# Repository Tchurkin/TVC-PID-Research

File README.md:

# Quantifying Stability Boundaries for Amateur TVC Rockets (STS 2027)

This repository builds and validates a free, open-source **stability-mapping and preflight workflow** for small thrust-vector-control rockets. The goal is to replace hobbyist "tune until it flies" practice with a quantitative answer to a harder question: is a candidate rocket easy, fragile, or fundamentally infeasible given its real actuator and airframe?

## Mission
Give amateur and student TVC builders a quantitative preflight answer before they fly: is this rocket stabilizable at all, what hardware parameters matter most, and what starting gains are justified by the measured actuator rather than copied from another project.

## Core Contribution
This project does **not** claim new control theory. It contributes a *measurement-to-decision pipeline* and a quantitative stability map that do not currently exist in the amateur TVC community:
1. Bench measurement of loaded actuator slew, travel, deadband, and backlash.
2. Realistic flight model with documented sensor and actuator nonidealities.
3. Empirically calibrated easy / fragile / infeasible regime map plus GO / MARGINAL / NOGO classifier.
4. Bench-calibrated PD autotuner that beats copied or over-clean-sim gains in the workable region.
5. Regime-specific sim-to-real ablation that tells builders which parts of the reality gap actually matter where.
6. An explicitly secondary severe-collapse controller appendix, kept only where it survives honest stress tests.

## Headline Results (simulation-side, May 2026)
- **Scaling law:** required loaded slew rate ≈ `0.32 · p^2` (R² = 0.75), matching inverted-pendulum theory.
- **Firmware audit:** three publicly deployed open-source TVC firmwares all fail predictably on statically unstable airframes with their shipped PID gains.
- **Validator calibration** on held-out random configs: GO precision 91%, NOGO precision 100%.
- **Measured-aware tuning:** measured-plant PD beats naive-sim or copied-gain baselines in several hard cells.
- **Regime-aware realism screen:** actuator nonlinearity dominates the actuator-limited regime; sensor noise and effectiveness drift dominate near the boundary.
- **Hobby-range controller check:** in `experiments/results/pid_slew_regime_summary.csv`, a best-tuned sweep over nominal loaded slew 45-90 deg/s, `p = 4, 6, 8`, and retained slew scales 1.00-0.25 yields `48/48 BOTH_FINE` for PID and PID_SLEW_AWARE.
- **Severe-collapse appendix:** in the explicit legacy stress probe `experiments/results/pid_slew_probe.csv`, the lightweight slew-aware PID branch can still rescue some low-slew collapse cells, but that is no longer the main claim.

Current nominal sim stack: 75 deg/s loaded gimbal slew. The old ~15 deg/s stack is retained only in explicit severe-collapse controller stress scripts.

## Workspace Map
- `experiments/` — main evidence-generation scripts (validator, scaling law, ablations, comparisons) and `experiments/validator/recommend_envelope.m`.
- `experiments/run_pid_slew_regime_map.m` — honest hobby-range check for whether the lightweight controller matters once the nominal actuator is realistic.
- `experiments/results/` — CSVs and PNGs for every claim; `experiments/results/graphs/preflight_workflow.png` is the headline figure.
- `tools/bench_to_validator.m`, `tools/bench_to_autotune.m`, `tools/process_gimbal_bench_test.m` — bench-CSV → validator pipeline.
- `Firmware/feedback_servo_calibration.ino` — bench-rig firmware (analog-feedback servo data).
- `ModelRocket_Adaptive_TVC/src/simulate_case_realistic.m` — realistic flight simulator.
- `paper/Tentative_Paper_Draft.md`, `paper/Mentor_Project_Summary.md` — current paper framing.
- `data/bench/` — bench-test templates and (eventually) real measurements.

Older directories (`Direction_B_RC_ADRC_PathFollow/`, `supporting/Direction_C_Companion/`) are exploratory branches from earlier directions; they are retained for reference but are not on the current primary path.

## Quick Start
### Regenerate the headline figures
```powershell
cd experiments
& "C:/Program Files/MATLAB/R2026a/bin/matlab.exe" -batch "generate_preflight_workflow_figure; generate_phase_diagram_reference_vehicles; run_current_vs_proposed_practice; generate_preflight_story_figures;"
```

### Run the bench-to-autotune bridge on a bench CSV
```matlab
addpath(genpath('tools'));
addpath(genpath('ModelRocket_Adaptive_TVC/src'));
addpath('experiments/validator');
result = bench_to_autotune('data/bench/gimbal_bench_test_template.csv');
disp(result);
```

### Rebuild all simulator-side sweeps (slow)
```powershell
cd experiments
& "C:/Program Files/MATLAB/R2026a/bin/matlab.exe" -batch "run('run_s2r_ablation.m'); run('run_p_estimation_error.m'); run('run_basic_vs_better_sim.m');"
```

## Direction Anchor Files
- `paper/Tentative_Paper_Draft.md` — the paper draft (builder-voice abstract + intro).
- `paper/Mentor_Project_Summary.md` — short mentor-facing summary.
- `experiments/HEADLINE_FINAL.md` — locked simulator-side findings.
- `experiments/results/graphs/preflight_workflow.png` — one-page workflow diagram.
- `experiments/results/graphs/phase_diagram_reference_vehicles.png` — phase diagram with hobbyist reference dots.

## STS Framing
This is positioned as a *quantitative stability-boundary and preflight workflow paper for an underserved community*, not as a new-controller paper. The right STS comparison set is past finalists who built useful, reproducible, community-facing engineering artifacts and validated them with real measurements — not past finalists who claimed new physics or new control theory. The lightweight controller branch is now explicitly appendix-level unless future hardware data proves otherwise.

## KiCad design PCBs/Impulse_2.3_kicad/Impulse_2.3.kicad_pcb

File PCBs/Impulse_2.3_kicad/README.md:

# Impulse 2.3 — upsized pyro switching path

Forked from the **ordered** Impulse 2.2 files (the state manufactured 2026-08-01) on 2026-08-12,
after **Q21, the pyro rail ARM switch, burned out on the bench**. Revised 2026-08-13 once the
initiator was actually measured.

## The design point moved

The initiator measures **~0.3 Ω**, not the ~1 Ω the firmware comments assumed. That puts the firing
loop at **12–17 A**, against the 2–4 A the 2026-07-23 log entry sized the board for. At 14 A held for
the firmware's 900 ms:

| part | P | ΔT over 900 ms | verdict |
|---|---|---|---|
| AO3401A SOT-23 (the part that died) | 16.5 W | ~2100 °C | obliterated — fully explains the failure |
| CSD17313Q2 SON 2×2 (original firing FETs) | 11.5 W | ~254 °C | **would also fail** on a sustained pulse |

So the whole switching path is upsized, not just the part that died.

## What changed

Nothing outside these **six** parts: a netlist diff against 2.2 shows **77 nets in both, none added
or removed, and zero membership changes outside the swapped FETs**.

| | 2.2 | 2.3 |
|---|---|---|
| Q20 main battery switch (P-ch) | AO3401A, SOT-23 | **AON6403**, DFN 5×6 — LCSC **C2760089** |
| Q21 arm switch (P-ch) | AO3401A, SOT-23 | **AON6403**, DFN 5×6 — LCSC **C2760089** |
| Q21 R<sub>DS(on)</sub> | 60 mΩ @ −4.5 V | **4.3 mΩ @ −4.5 V** |
| Q16–Q19 firing FETs (N-ch) | CSD17313Q2, SON 2×2 | **CSD17301Q5A**, SON 5×6 — LCSC **C129940** |
| Q16–Q19 R<sub>DS(on)</sub> | 42 mΩ @ 3 V | **2.9 mΩ @ 3 V** |
| loop on-resistance | 84 mΩ hot | **10 mΩ hot** |
| drain → connector | trace | trace (see correction below) |
| pyro rail copper | 1.0 mm | 1.2–2.5 mm |

At 20 A / 900 ms the two halves are **matched**: **2.4 W** in each AON6403 (Tj ≈ 44 °C; survives the
pulse *indefinitely* — Tj ≈ 121 °C even at steady state) and **2.1 W** in each CSD17301Q5A
(Tj ≈ 48 °C). Neither is the weak half.

Lower R<sub>DS(on)</sub> does **not** buy more current — at 0.3 Ω the FETs are only ~4 % of the loop,
so the initiator and pack internal resistance set it. What it buys is thermal margin, which is why
the firing FETs are the 2.9 mΩ CSD17301Q5A rather than the 9.5 mΩ CSD17302Q5A (5.3 W, Tj ≈ 84 °C —
the weak half). The 17301 also carries **414 mJ E<sub>AS</sub> vs 61 mJ**, the margin that absorbs the
inductive kick when the nichrome opens ~20 A. Same footprint, same pin map, so it cost no layout.

> **The CSD17301Q5A's 2.9 mΩ is guaranteed at V<sub>GS</sub> = 3 V.** That is the binding
> requirement — the Teensy drives these gates directly, with no gate driver. Never substitute a part
> specified only at 4.5 V. (And never a P-channel: Q16–Q19 are low-side switches with sources at GND.)

## Layout notes

- The firing FETs are placed at **rot 270** so each 4.6 × 4.7 mm drain tab sits directly over its
  connector's pin-1 pad. Same net, so the firing current gets a **zero-length connection instead of
  a trace**, and the gate lands south-east facing the incoming PYROn traces.
- They shifted north to y = 45.5 to clear a via field (CS_IMU, INT_IMU, GPS_RX, PYRO_SW) that the
  lead rows had landed on. Q17 also sits east of its connector because the PI battery header
  occupies its natural spot.
- Q21 rotated 90° with its tab north — this also improved its side clearance from 0.48 mm to ~1.4 mm.
- ⚠ **CORRECTED 2026-08-18.** This file previously claimed each drain tab *overlaps* its connector's
  pin-1 pad, making every `Net-(PnO-Pin_1)` track "continuity-sense only (~0.6 mA)" and justifying
  narrowing them to 0.3 mm. **Measured: they are 3.13 mm apart on every channel — they never
  overlapped.** Those 0.3 mm tracks were therefore carrying the full ~18 A firing current, against an
  IPC-2221 1 oz rating of 1.0 A. On re-route, the FET-tab→connector run must be ≥1.5 mm; only the
  long runs to R37/R41/R42/R43 are genuinely sense-only.

## Verification

| check | 2.2 baseline | 2.3 (re-routed 2026-08-18) |
|---|---|---|
| ERC errors | 0 | **0** |
| DRC schematic parity | 0 | **0** |
| clearance / shorts / edge / hole / mask-bridge / dangling | 0 | **0** |
| courtyard overlaps | 20 | **20** |
| pth_inside_courtyard | 14 | **14** |
| stranded pads | 0 | **0** |
| GND pour fragments (pad-less, cosmetic) | — | 3 |

Netlist vs 2.2: 77 nets both, none added or removed, **zero membership changes outside the six FETs**.

After the 2026-08-18 re-placement both counts match the 2.2 baseline exactly. Silk warnings are cosmetic.

## Re-route (2026-08-18)

The board was unrouted, 27 footprints re-placed by hand, then re-routed:

- **freerouting 2.2.4** (JRE 25, spaceless path) took 155 nets to **2 unrouted** in 2m46s. GND was
  left to the pours by exporting the zones as DSN `(plane ...)` blocks.
- The 2 it refused were both **low-current nets carrying a power netclass width**: VBAT is MAIN_PWR
  (1.2 mm) but U3 pin 5 is the buck's **ENABLE** pin (microamps, and 1.2 mm will not thread a
  SOT-23-6 pin field), and `Net-(P4O-Pin_1)` is PYRO_DRAIN (1.0 mm) but the R42 leg is the
  continuity **sense** branch (~0.6 mA). freerouting never necks below the class width. Both were
  hand-routed at signal width — VBAT with a 2-via B.Cu hop under the buck, P4O with a grid A*
  route (`_route_astar.py`, 69 segments / 3 vias, 64.6 mm) whose every segment was then re-verified
  with the exact checker.
- `_widen_rails.py` then widened 70 pyro segments. **The firing path (FET drain tab → connector
  pin 1) is now 2.50 mm on all four channels** — 4.6 A IPC steady, ~42 °C adiabatic rise at 18 A
  over 200 ms. It was 0.30 mm before (1.0 A rated), which was the defect described above.
- GND pours stitched with 39 **pour-aware** vias. A naive grid stitch was tried first and was worse
  (16 dangling vias in voids, 10 edge violations) because clearance-checking a via says nothing
  about whether copper exists there; the working version reads the filled polygons back and only
  places a via that lands inside real pour on 2+ layers.

3 pad-less GND pour fragments remain — floating copper, no stranded pads, same class of cosmetic
item this project documented on the sensor board.

## Before ordering

Read `fab/ORDER_NOTES.txt`. The thing that genuinely needs a human eye:

> **Rotations for all six FETs are unverified.** These are new custom footprints, so none of 2.2's
> hand-converged JLC rotation calibration carries over. The CPL emits Q21 = 90 (top),
> Q16–Q19 = 90 and Q20 = 180 (bottom). Check all six in JLC's preview against the silk pin-1 ticks — this
> project's notes call the JLC preview the only ground truth, and a 180° error on a pyro FET is a
> dead channel or one that fires on power-up.

Pin maps differ between the two packages, and swapping them would be fatal:

```
AON6403      pads 1,2,3 = SOURCE   pad 4 = GATE   pad 5 = DRAIN tab
CSD17301Q5A  pad 1 = DRAIN tab     pad 5 = GATE   pads 6,7,8 = SOURCE
```

Both derive from KiCad's `PQFN-8-EP_6x5mm_P1.27mm_Generic` land pattern, whose own description names
exactly these two packages.

## Firmware implication

At 14 A the wire itself dissipates **~59 W**, so it cuts far faster than the 900 ms the firmware
holds the channel on. The silicon now survives that, but holding on after the cut still sags the pack
to ~6.2–6.8 V. Measure the actual cut time and shorten the pulse; keep the burst-fire logic in
`Impulse22_PyroTest.ino` as defence in depth.

## Scripts (in order)

| script | what it does |
|---|---|
| `_mk23.py` | fork 2.2 → 2.3 (copy, rename, rewrite 214 internal references) |
| `_mk_fp_5x6.py` | generate the two 5×6 footprints into `Impulse22.pretty` |
| `_upsize_pyro_silicon.py` | schematic: swap all 6 FET symbols + pin maps |
| `_place_pyro_fets.py <ref> [--force\|--probe <rot>]` | PCB footprint swap + placement (one per process) |
| `_guard_placement.py snapshot\|repair <pcb> <json> [ref]` | **run around every pcbnew placement** — catches collateral footprint movement |
| `_route_q20.py --cut/--check/--add` | Q20 gate/source copper + removal of the obsolete VBAT stub |
| `_fab_q20.py` | patch BOM/CPL for Q20 and rezip gerbers |
| `_reroute_upsized.py --cut/--check/--add` | pyro re-route around the new packages |
| `_fix_route_conflicts.py --cut/--check/--add` | resolve collisions *between* the new tracks |
| `_widen_rails.py` | widen the rail against live geometry and the board outline |
| `_refill_zones.py` | re-pour the 4 GND zones (KiCad python) |
| `_dump_geom.py` / `_geom.py` / `_fp_extent.py` | pcbnew geometry dump + clearance checker |

`_dump_geom.py`, `_refill_zones.py`, `_fp_extent.py` and `_place_pyro_fets.py` need KiCad's
interpreter (`C:/Program Files/KiCad/10.0/bin/python.exe`); the rest run on system Python.

## Three things the routing taught

1. **Check new copper against the *pending* set, not just the existing board.** Sizing/placing each
   addition against the pre-batch board let additions collide with each other — it produced a real
   PYRO1↔PYRO_G short and a via sitting on a rail. This bit twice (also in the widening pass, which
   produced a P3O↔7.4V short and a trace 0.383 mm from the 35 mm-radius edge).
2. **Scan for legal vias; don't reason about them.** `In2` carries a board-wide horizontal signal bus
   (CS_IMU 51.564, SENS_DET 52.374, INT_IMU 53.183, MISO 54.038) whose 0.81 mm gaps fit no via. That
   single fact invalidates whole classes of route, and a 2-D scan finds it in seconds.
3. **Take footprint geometry from pcbnew, never from parsing.** A hand-rolled parser got the
   rotation *sign* wrong and reported R67's two pads with their nets swapped — which would have been
   a real short.

## Q20 — done (2026-08-17)

Q20, the main battery switch, is now the **same AON6403 as Q21**, so it shares the feeder and adds
no BOM line — and **AO3401A is gone from the board entirely**. It was a **single point of failure
for the whole avionics stack** (the Teensy that fires the chute is powered through it), and a
sustained multi-servo stall sat it at ~0.43 W in SOT-23 → **Tj ≈ 135 °C continuously**, not for a
900 ms pulse. At 4.3 mΩ that is ~0.03 W.

It moved to **(175.700, 79.500) rot 0** on B.Cu, east of the buzzer: its old pocket has only 4.52 mm
between the BUZZER's through-hole pads and R66, and a DFN5x6 needs 4.96 plus clearance. East is free
because **VBAT already left Q20 eastward** (to C39, then via In2 round to R54/U2/U3), so the drain
tab now sits on the path it already took; only VBAT_RAW lengthens (~4 mm, ≈2 mΩ). The gate takes a
two-via In1 jog, same reason as Q21's — it sits on the far side of the source-pad column.

Q20 added **zero** new DRC items: courtyard 21 and pth_inside_courtyard 18, identical to the pre-Q20
baseline.

## ⚠ Recovery note — the board was found broken on 2026-08-17

At the start of that session `Impulse_2.3.kicad_pcb` was in an **unverified, broken state**: 15
unconnected and 136 DRC errors, with Q16–Q19 displaced ~3 mm south onto the CS_IMU/INT_IMU via field
that the y=45.5 placement exists to avoid, Q21's rotation reset 90 → 0, and PI/C15/R67/R68 shifted.
The last verified-clean artifact was `drc_mag_main.json` (2026-08-15).

Recovery was: restore `Impulse_2.3.kicad_pcb.pre_mag`, re-apply the `GPS_PPS`→`CS_MAG` rename, redo
Q20. The broken state is preserved as `Impulse_2.3.kicad_pcb.corrupt_20260817` in case any of it was
wanted. **If you deliberately re-placed those parts on 2026-08-16, that work is in the corrupt file
and was discarded here — say so and it can be re-applied properly.**

The lesson is now enforced in code: a pcbnew `LoadBoard/Remove/Add/SaveBoard` cycle is **not** a safe
no-op for the rest of the board, so `_guard_placement.py` snapshots every footprint's `(at x y rot)`
before such a run and restores anything that moved.

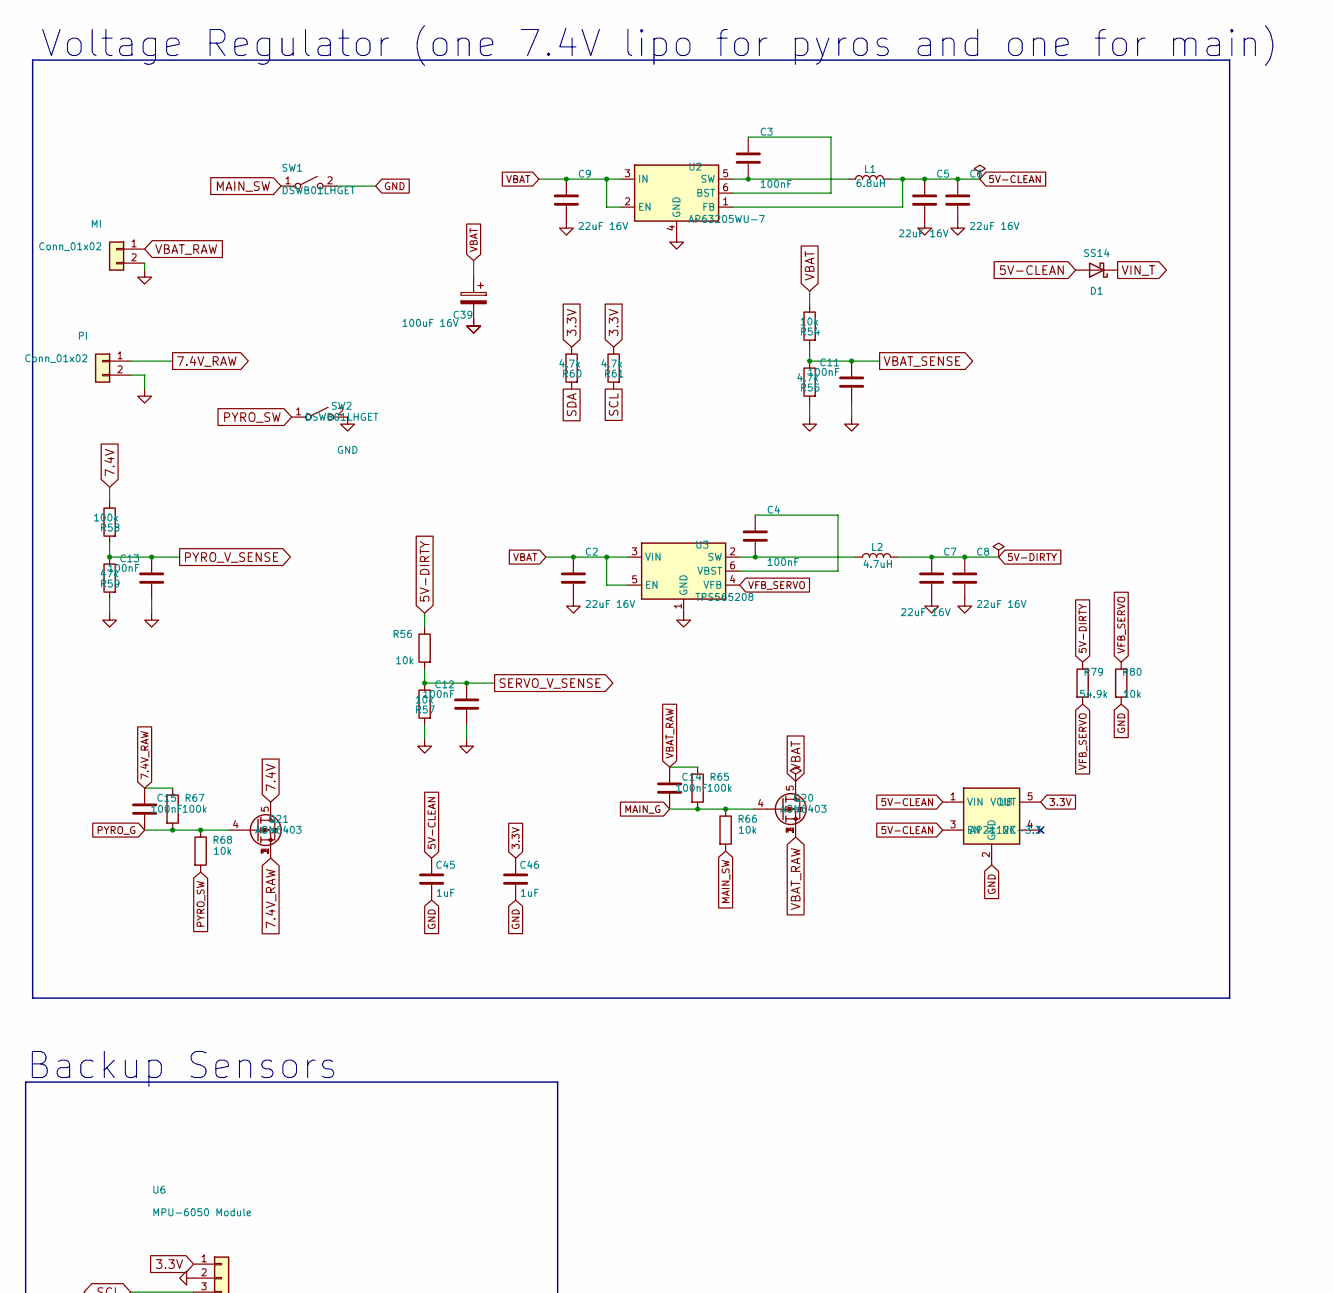
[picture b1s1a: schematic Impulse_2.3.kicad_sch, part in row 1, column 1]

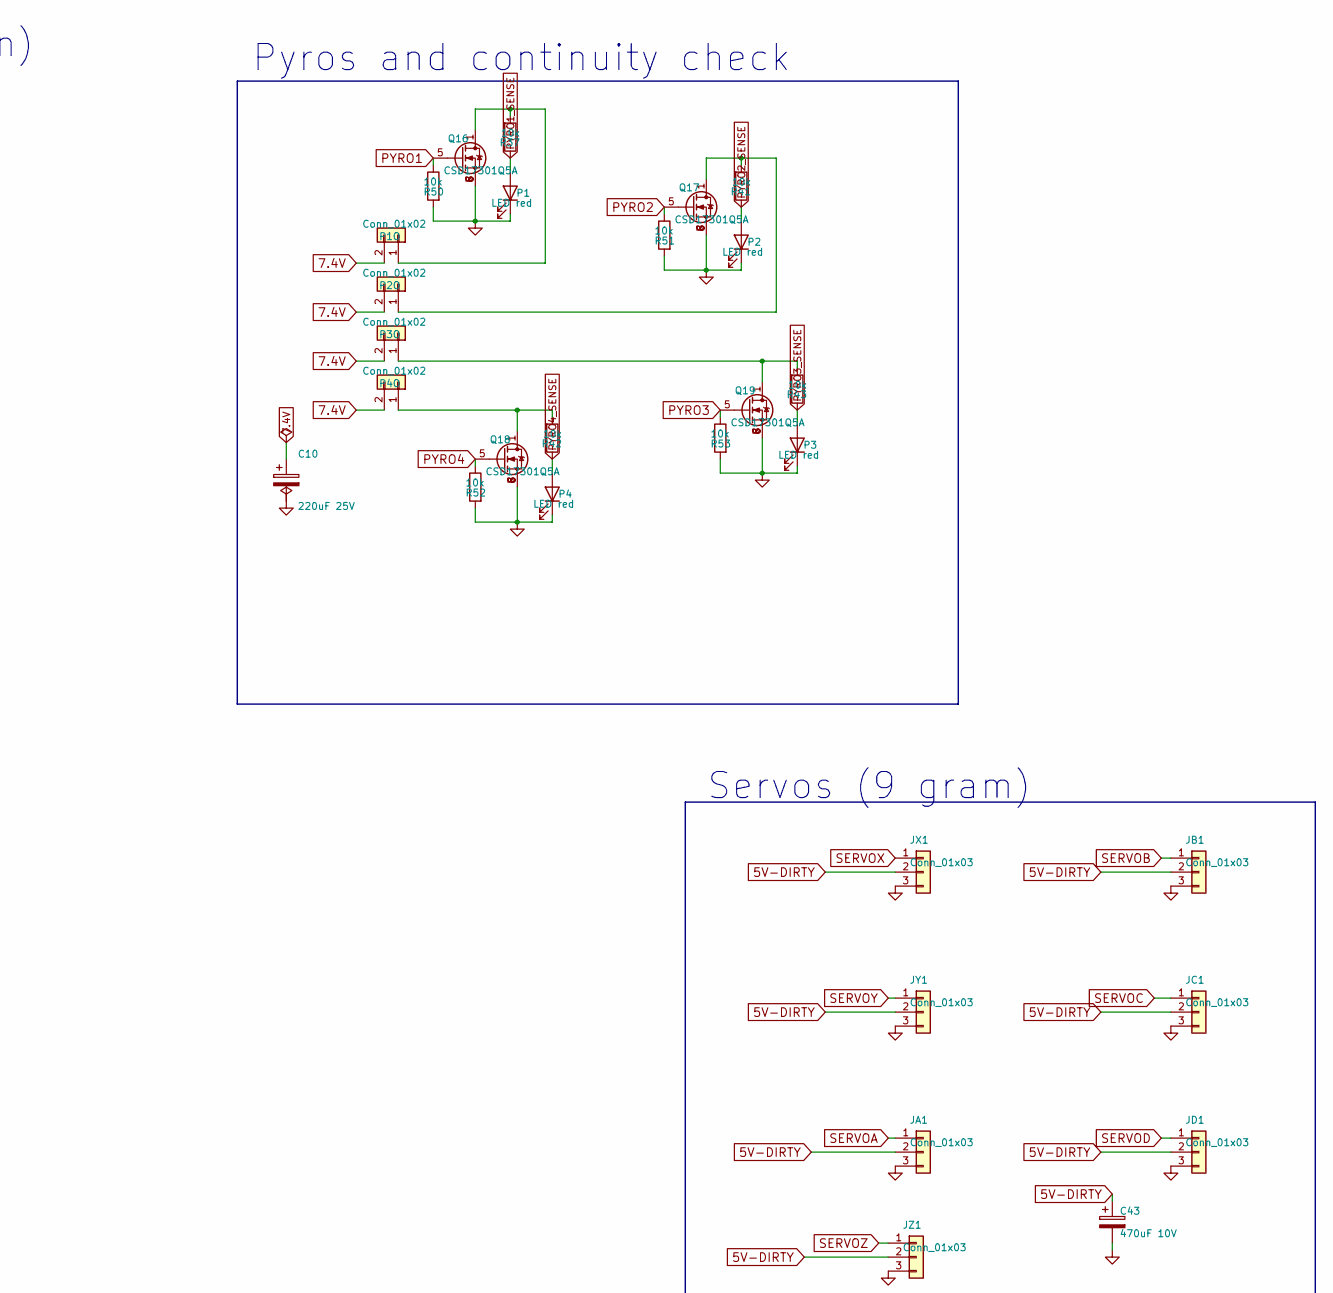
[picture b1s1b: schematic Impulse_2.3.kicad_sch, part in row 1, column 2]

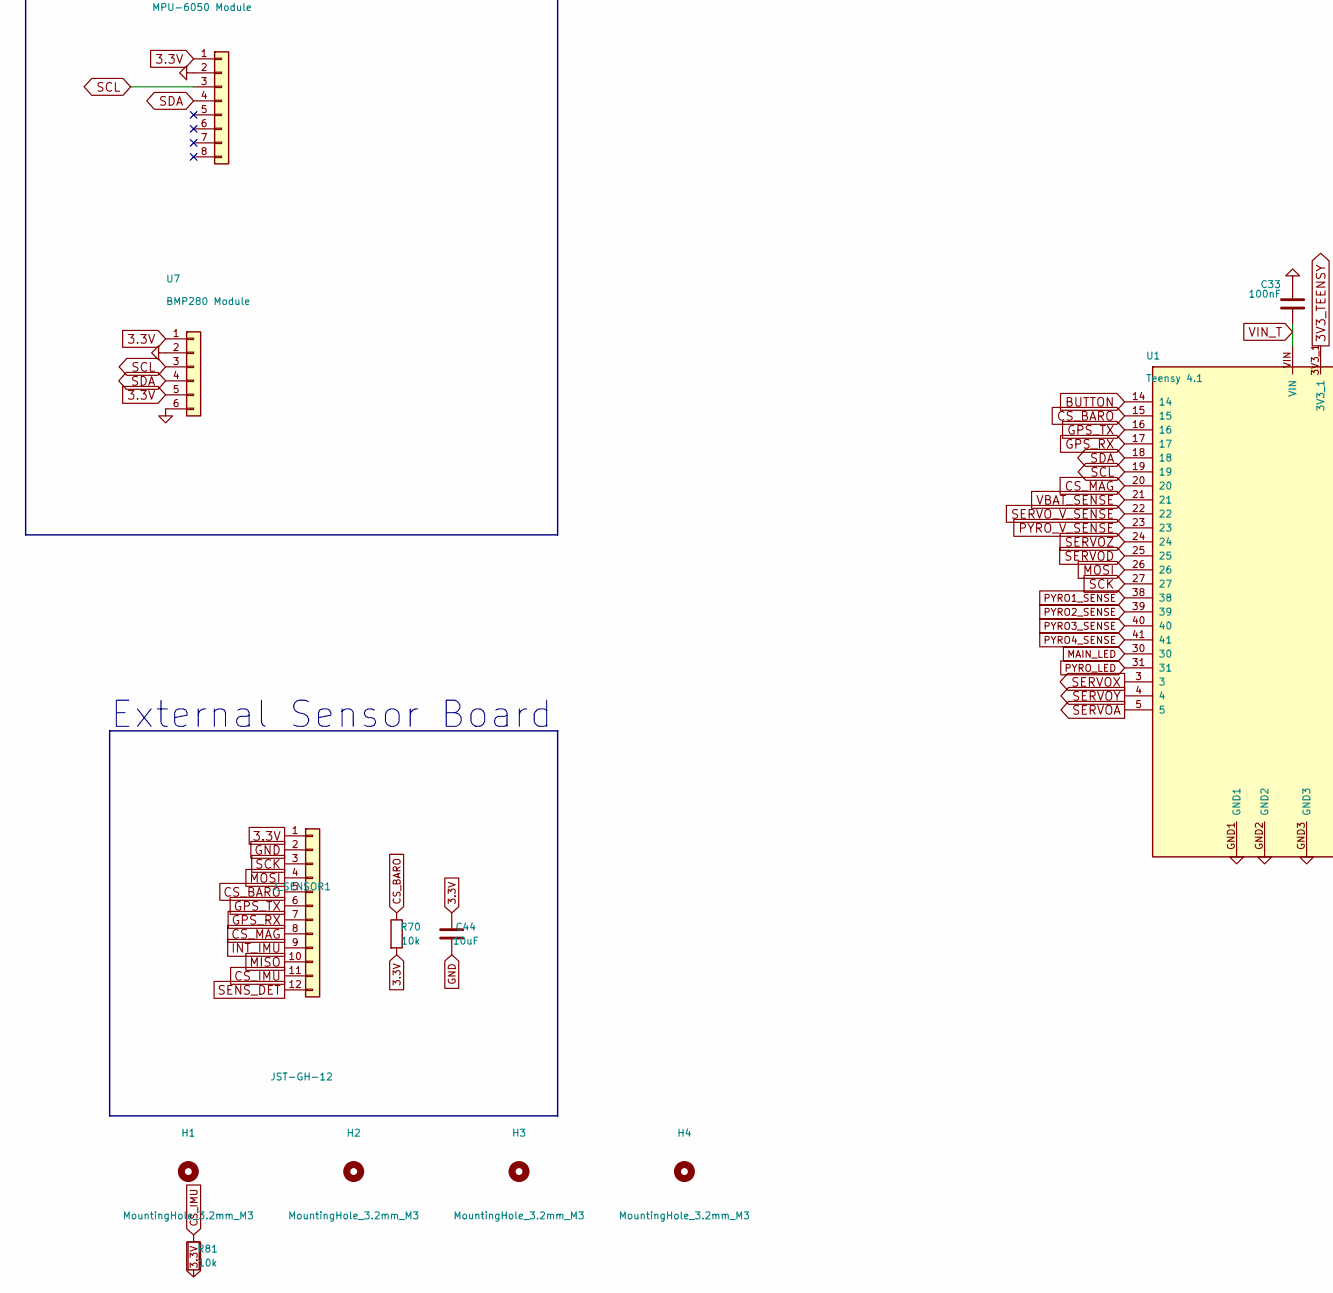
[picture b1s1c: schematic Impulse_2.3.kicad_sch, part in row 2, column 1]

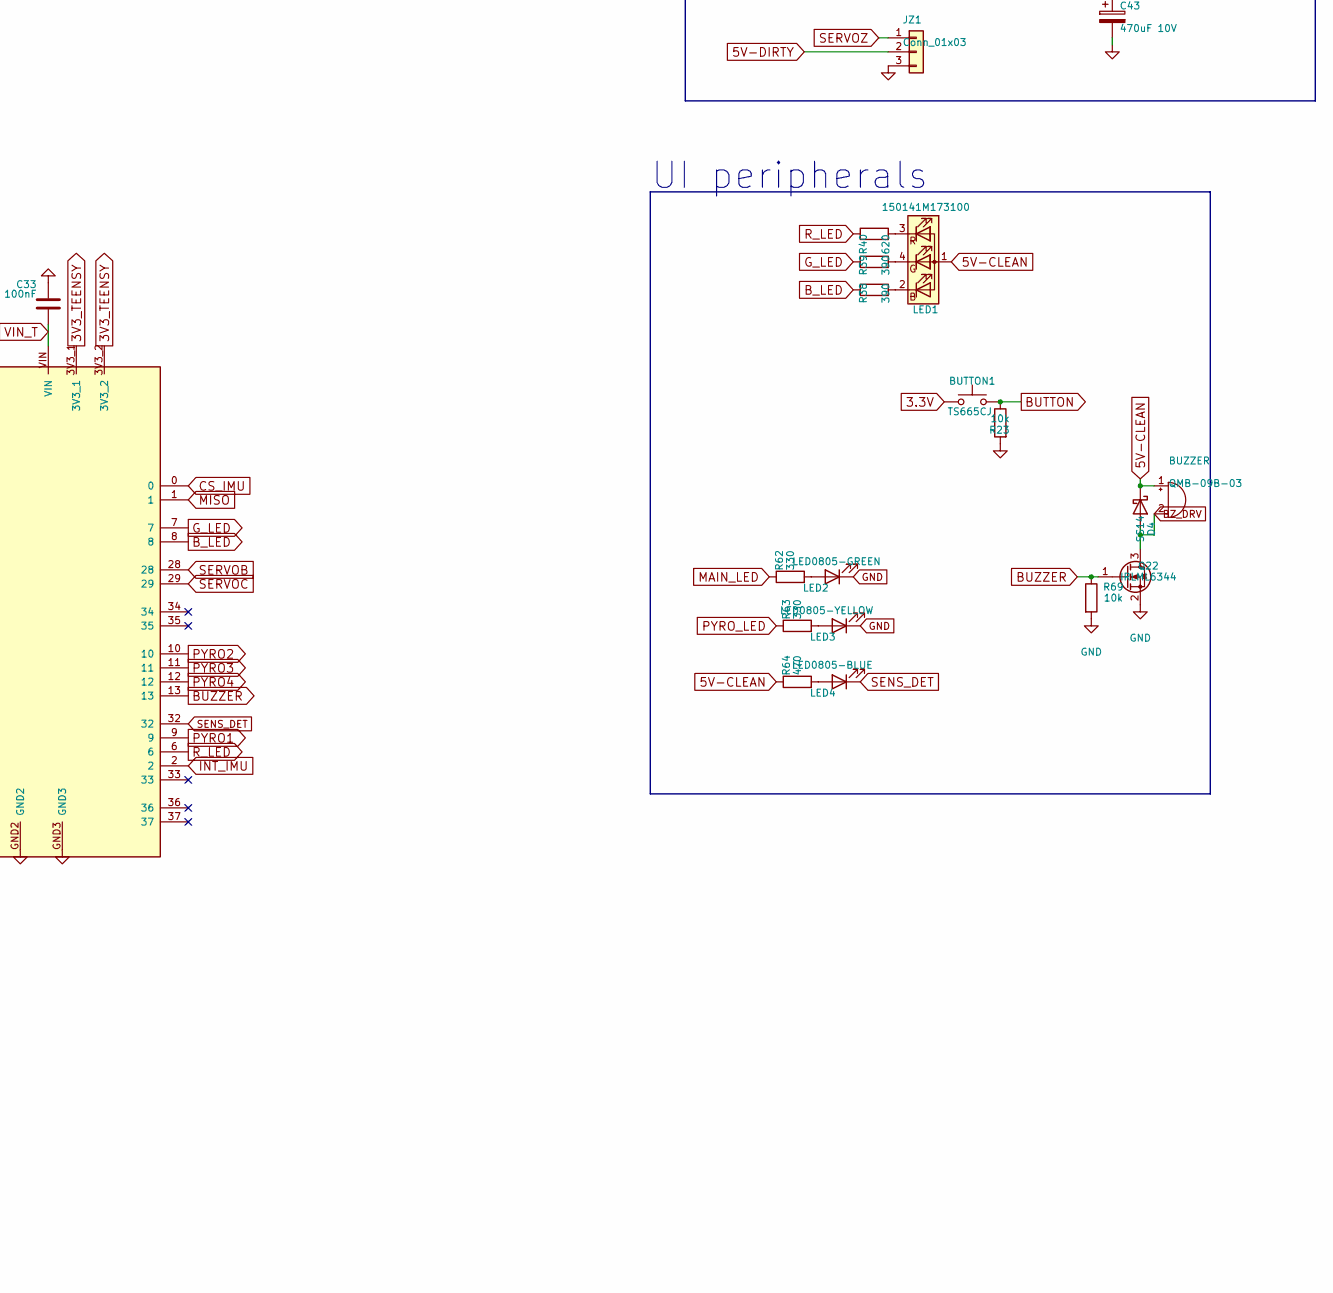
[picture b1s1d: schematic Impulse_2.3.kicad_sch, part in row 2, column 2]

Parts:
BUTTON1: TS665CJ; SW_PUSH_6mm
BUZZER: QMB-09B-03; Buzzer_D9.0mm_P4.00mm
C2, C5, C6, C7, C8, C9: 22uF 16V; C_1206_3216Metric
C3, C4, C11, C12, C13, C14, C15, C33: 100nF; C_0603_1608Metric
C10: 220uF 25V; CP_Elec_8x10
C39: 100uF 16V; CP_Elec_6.3x7.7
C43: 470uF 10V; CP_Elec_6.3x7.7
C44: 10uF; C_0805_2012Metric
C45, C46: 1uF; C_0603_1608Metric
D1, D4: SS14; D_SMA
H1, H2, H3, H4: MountingHole_3.2mm_M3
JA1: Conn_01x03; PinHeader_1x03_P2.54mm_Vertical
JB1: Conn_01x03; PinHeader_1x03_P2.54mm_Vertical
JC1: Conn_01x03; PinHeader_1x03_P2.54mm_Vertical
JD1: Conn_01x03; PinHeader_1x03_P2.54mm_Vertical
JX1: Conn_01x03; PinHeader_1x03_P2.54mm_Vertical
JY1: Conn_01x03; PinHeader_1x03_P2.54mm_Vertical
JZ1: Conn_01x03; PinHeader_1x03_P2.54mm_Vertical
J_SENSOR1: JST-GH-12; JST_GH_BM12B-GHS-TBT_1x12-1MP_P1.25mm_Vertical
L1: 6.8uH; L_Bourns_SRN6045TA
L2: 4.7uH; L_Bourns_SRN6045TA
LED1: 150141M173100; LED_RGB_Wuerth-PLCC4_3.2x2.8mm_150141M173100
LED2: LED0805-GREEN; LED_0805_2012Metric
LED3: LED0805-YELLOW; LED_0805_2012Metric
LED4: LED0805-BLUE; LED_0805_2012Metric
MI: Conn_01x02; PinHeader_1x02_P2.54mm_Vertical
P1, P2, P3, P4: LED red; LED_0805_2012Metric
P1O, P2O, P3O, P4O: Conn_01x02; Molex_Micro-Fit_3.0_43045-0212_2x01_P3.00mm_Vertical
PI: Conn_01x02; PinHeader_1x02_P2.54mm_Vertical
Q16, Q17, Q18, Q19: CSD17301Q5A; TI_SON5x6_Q5A
Q20, Q21: AON6403; AON6403_DFN5x6
Q22: IRLML6344; SOT-23
R23, R37, R41, R42, R43, R50, R51, R52, R53, R54, R56, R57, R66, R68, R69, R70, R80, R81: 10k; R_0603_1608Metric
R38, R39: 390; R_0603_1608Metric
R40: 620; R_0603_1608Metric
R55, R60, R61: 4.7k; R_0603_1608Metric
R58, R65, R67: 100k; R_0603_1608Metric
R59: 47k; R_0603_1608Metric
R62, R63: 330; R_0603_1608Metric
R64: 470; R_0603_1608Metric
R79: 54.9k; R_0603_1608Metric
SW1, SW2: DSWB01LHGET; SW_DIP_SPSTx01_Slide_6.7x4.1mm_W7.62mm_P2.54mm_LowProfile
U1: Teensy 4.1; TEENSY41
U2: AP63205WU-7; TSOT-23-6
U3: TPS565208; SOT-23-6
U6: MPU-6050 Module; PinHeader_1x08_P2.54mm_Vertical
U7: BMP280 Module; PinHeader_1x06_P2.54mm_Vertical
U8: AP2112K-3.3; SOT-23-5

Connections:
3.3V: BUTTON1.1, C44.1, C46.1, J_SENSOR1.1, R60.1, R61.1, R70.2, R81.2, U6.1, U7.1, U7.5, U8.5 (VOUT)
3V3_TEENSY: U1.3V3_1, U1.3V3_2
5V-CLEAN: BUZZER.1 (+), C5.1, C6.1, C45.1, D1.2 (A), D4.1 (K), L1.2, LED1.1 (A), R64.1, U2.1 (FB), U8.1 (VIN), U8.3 (EN)
5V-DIRTY: C7.1, C8.1, C43.1, JA1.2, JB1.2, JC1.2, JD1.2, JX1.2, JY1.2, JZ1.2, L2.2, R56.1, R79.1
7.4V: C10.1, P1O.2, P2O.2, P3O.2, P4O.2, Q21.5 (D), R58.1
7.4V_RAW: C15.1, PI.1, Q21.1 (S), Q21.2 (S), Q21.3 (S), R67.1
BUTTON: BUTTON1.2, R23.1, U1.14
BUZZER: Q22.1 (G), R69.1, U1.13
BZ_DRV: BUZZER.2 (-), D4.2 (A), Q22.3 (D)
B_LED: R38.1, U1.8
CS_BARO: J_SENSOR1.5, R70.1, U1.15
CS_IMU: J_SENSOR1.11, R81.1, U1.0
CS_MAG: J_SENSOR1.8, U1.20
GND: C2.2, C5.2, C6.2, C7.2, C8.2, C9.2, C10.2, C11.2, C12.2, C13.2, C33.1, C39.2, C43.2, C44.2, C45.2, C46.2, JA1.3, JB1.3, JC1.3, JD1.3, JX1.3, JY1.3, JZ1.3, J_SENSOR1.2, LED2.1 (K), LED3.1 (K), MI.2, P1.1 (K), P2.1 (K), P3.1 (K), P4.1 (K), PI.2, Q16.6 (S), Q16.7 (S), Q16.8 (S), Q17.6 (S), Q17.7 (S), Q17.8 (S), Q18.6 (S), Q18.7 (S), Q18.8 (S), Q19.6 (S), Q19.7 (S), Q19.8 (S), Q22.2 (S), R23.2, R50.2, R51.2, R52.2, R53.2, R55.2, R57.2, R59.2, R69.2, R80.2, SW1.2 (B), SW2.2 (B), U1.GND1, U1.GND2, U1.GND3, U2.4 (GND), U3.1 (GND), U6.2, U7.2, U7.6, U8.2 (GND)
GPS_RX: J_SENSOR1.7, U1.17
GPS_TX: J_SENSOR1.6, U1.16
G_LED: R39.1, U1.7
INT_IMU: J_SENSOR1.9, U1.2
MAIN_G: C14.2, Q20.4 (G), R65.2, R66.1
MAIN_LED: R62.1, U1.30
MAIN_SW: R66.2, SW1.1 (A)
MISO: J_SENSOR1.10, U1.1
MOSI: J_SENSOR1.4, U1.26
unnamed: LED1.2 (BK), R38.2
unnamed: LED1.4 (GK), R39.2
unnamed: LED1.3 (RK), R40.2
unnamed: LED2.2 (A), R62.2
unnamed: LED3.2 (A), R63.2
unnamed: LED4.2 (A), R64.2
unnamed: P1O.1, Q16.1 (D), R37.2
unnamed: P2O.1, Q17.1 (D), R41.2
unnamed: P3O.1, Q19.1 (D), R43.2
unnamed: P4O.1, Q18.1 (D), R42.2
unnamed: C3.1, U2.6 (BST)
unnamed: C3.2, L1.1, U2.5 (SW)
unnamed: C4.2, L2.1, U3.2 (SW)
unnamed: C4.1, U3.6 (VBST)
PYRO1: Q16.5 (G), R50.1, U1.9
PYRO1_SENSE: P1.2 (A), R37.1, U1.38
PYRO2: Q17.5 (G), R51.1, U1.10
PYRO2_SENSE: P2.2 (A), R41.1, U1.39
PYRO3: Q19.5 (G), R53.1, U1.11
PYRO3_SENSE: P3.2 (A), R43.1, U1.40
PYRO4: Q18.5 (G), R52.1, U1.12
PYRO4_SENSE: P4.2 (A), R42.1, U1.41
PYRO_G: C15.2, Q21.4 (G), R67.2, R68.1
PYRO_LED: R63.1, U1.31
PYRO_SW: R68.2, SW2.1 (A)
PYRO_V_SENSE: C13.1, R58.2, R59.1, U1.23
R_LED: R40.1, U1.6
SCK: J_SENSOR1.3, U1.27
SCL: R61.2, U1.19, U6.3, U7.3
SDA: R60.2, U1.18, U6.4, U7.4
SENS_DET: J_SENSOR1.12, LED4.1 (K), U1.32
SERVOA: JA1.1, U1.5
SERVOB: JB1.1, U1.28
SERVOC: JC1.1, U1.29
SERVOD: JD1.1, U1.25
SERVOX: JX1.1, U1.3
SERVOY: JY1.1, U1.4
SERVOZ: JZ1.1, U1.24
SERVO_V_SENSE: C12.1, R56.2, R57.1, U1.22
VBAT: C2.1, C9.1, C39.1, Q20.5 (D), R54.1, U2.2 (EN), U2.3 (IN), U3.3 (VIN), U3.5 (EN)
VBAT_RAW: C14.1, MI.1, Q20.1 (S), Q20.2 (S), Q20.3 (S), R65.1
VBAT_SENSE: C11.1, R54.2, R55.1, U1.21
VFB_SERVO: R79.2, R80.1, U3.4 (VFB)
VIN_T: C33.2, D1.1 (K), U1.VIN

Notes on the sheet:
Pyros and continuity check
Voltage Regulator (one 7.4V lipo for pyros and one for main)
UI peripherals
Servos (9 gram)
External Sensor Board
Backup Sensors

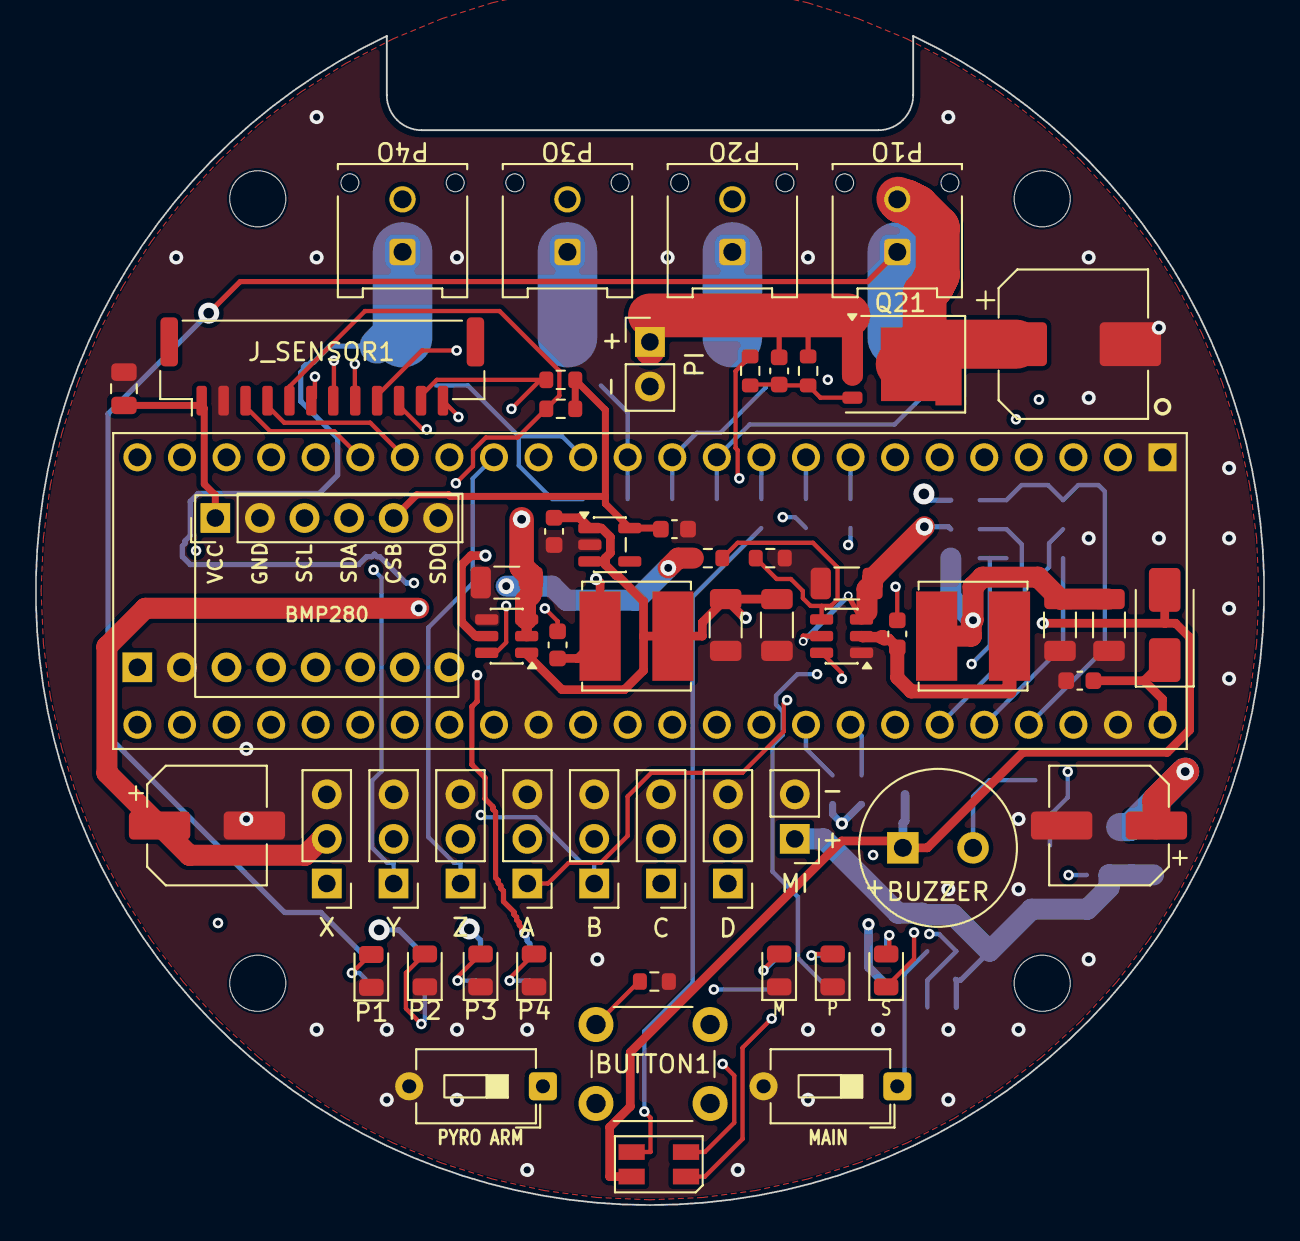
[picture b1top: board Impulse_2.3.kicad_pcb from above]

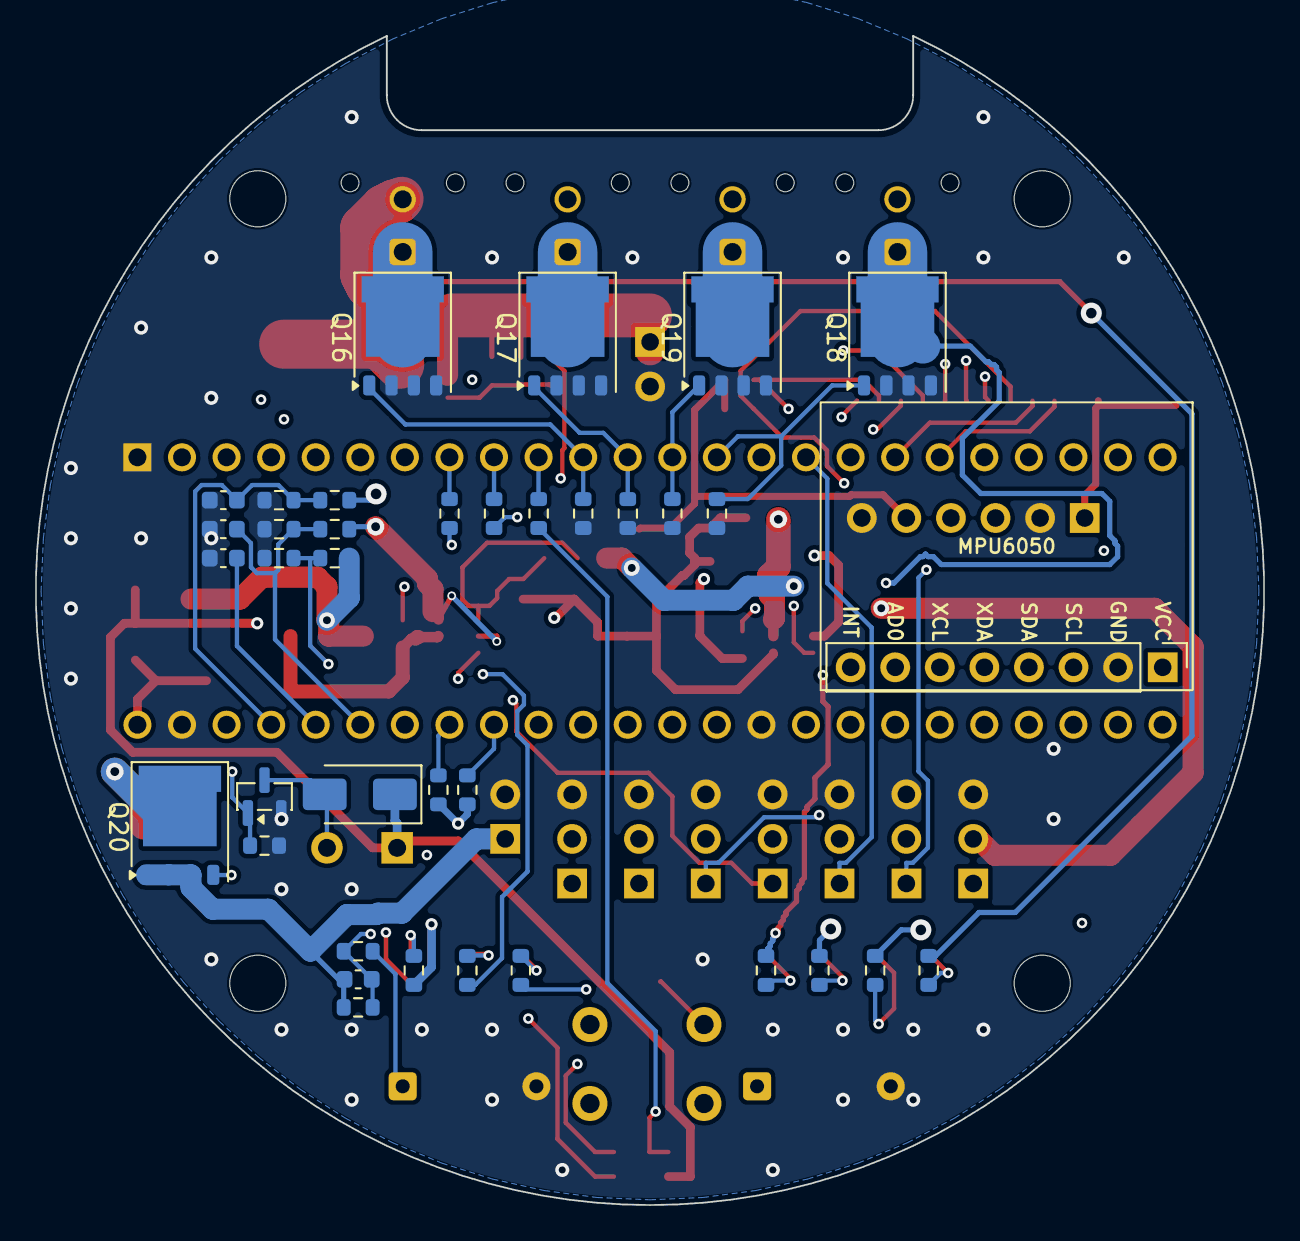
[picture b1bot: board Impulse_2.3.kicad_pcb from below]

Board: 4 copper layers, 70.0 x 66.6 mm, 99 parts (37 on the bottom side), 67 nets.

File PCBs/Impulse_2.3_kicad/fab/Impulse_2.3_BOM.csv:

Comment,Designator,Footprint,LCSC
100k,"R58,R65,R67",R_0603_1608Metric,
100nF,"C11,C12,C13,C14,C15,C3,C33,C4",C_0603_1608Metric,
100uF 16V,C39,CP_Elec_6.3x7.7,
10k,"R23,R37,R41,R42,R43,R50,R51,R52,R53,R54,R56,R57,R66,R68,R69,R70,R80,R81",R_0603_1608Metric,
10uF,C44,C_0805_2012Metric,
150141M173100,LED1,LED_RGB_Wuerth-PLCC4_3.2x2.8mm_150141M173100,
1uF,"C45,C46",C_0603_1608Metric,
220uF 25V 8x10,C10,CP_Elec_8x10,C165536
22uF 16V,"C2,C5,C6,C7,C8,C9",C_1206_3216Metric,
330,"R62,R63",R_0603_1608Metric,
390,"R38,R39",R_0603_1608Metric,
4.7k,"R55,R60,R61",R_0603_1608Metric,
4.7uH PNLS6045-4R7M,L2,L_Bourns_SRN6045TA,C2849535
470,R64,R_0603_1608Metric,
470uF 10V 6.3x7.7,C43,CP_Elec_6.3x7.7,C116423
47k,R59,R_0603_1608Metric,
54.9k,R79,R_0603_1608Metric,
6.8uH SWPA6045S6R8MT,L1,L_Bourns_SRN6045TA,C57254
620,R40,R_0603_1608Metric,
AON6403,"Q20,Q21",AON6403_DFN5x6 (DFN-8 5x6),C2760089
AP2112K-3.3,U8,SOT-23-5,
AP63205WU-7,U2,TSOT-23-6,
BM12B-GHS-TBT-LF-SN,J_SENSOR1,JST_GH_BM12B-GHS-TBT_1x12-1MP_P1.25mm_Vertical,C2983891
CSD17301Q5A,"Q16,Q17,Q18,Q19",TI_SON5x6_Q5A (SON 5x6),C129940
DSWB01LHGET,"SW1,SW2",SW_DIP_SPSTx01_Slide_6.7x4.1mm_W7.62mm_P2.54mm_LowProfile,
IRLML6344,Q22,SOT-23,
LED0805-BLUE,LED4,LED_0805_2012Metric,
LED0805-GREEN,LED2,LED_0805_2012Metric,
LED0805-YELLOW,LED3,LED_0805_2012Metric,
Molex Micro-Fit 3.0 43045-0212 2P 3.0mm vertical,"P1O,P2O,P3O,P4O",Molex_Micro-Fit_3.0_43045-0212_2x01_P3.00mm_Vertical,C22383211
Pin Header 1x3 2.54mm male vertical,"JA1,JB1,JC1,JD1,JX1,JY1,JZ1",PinHeader_1x03_P2.54mm_Vertical,C49257
Red LED 0805,"P1,P2,P3,P4",LED_0805_2012Metric,C84256
SS14,"D1,D4",D_SMA,C2480
TPS565208,U3,SOT-23-6,
TS665CJ,BUTTON1,SW_PUSH_6mm,
QMB-09B-03 passive buzzer 9mm THT,BUZZER,Buzzer_D9.0mm_P4.00mm,C96256

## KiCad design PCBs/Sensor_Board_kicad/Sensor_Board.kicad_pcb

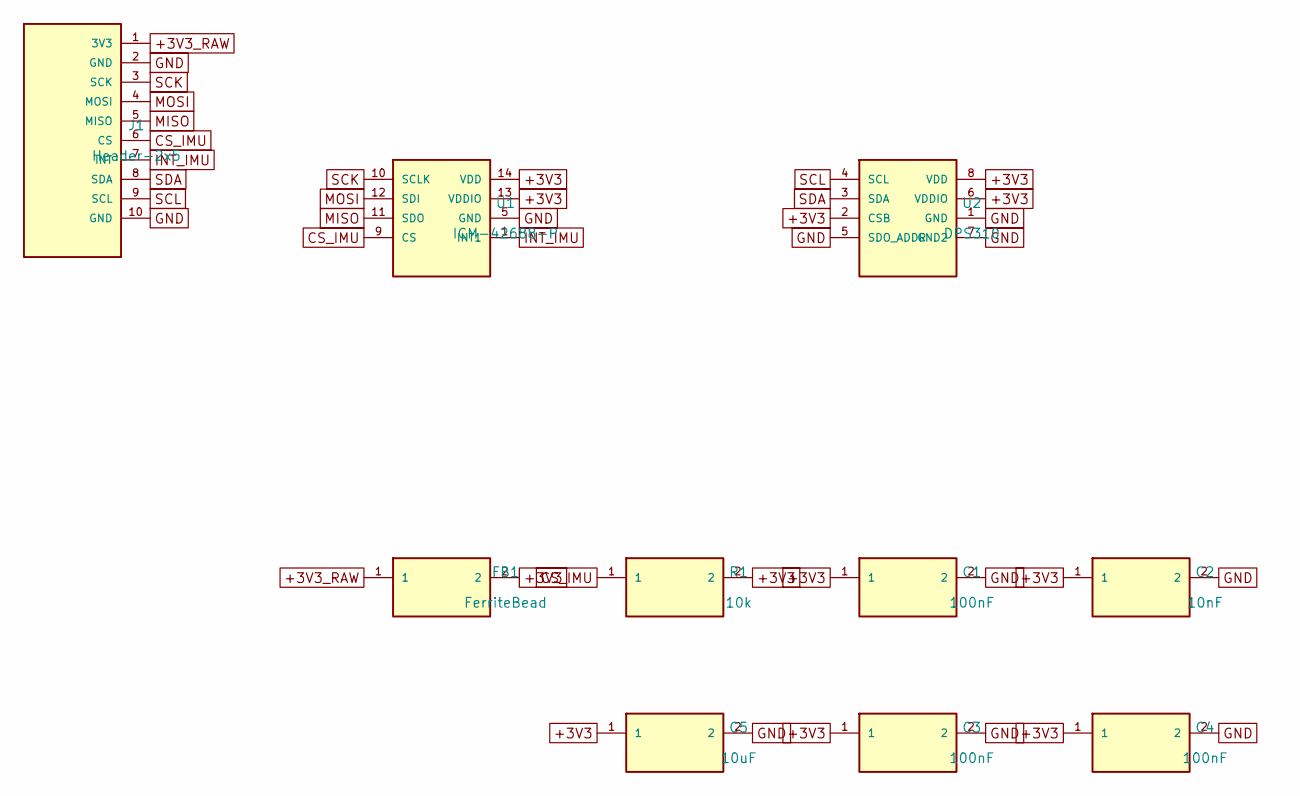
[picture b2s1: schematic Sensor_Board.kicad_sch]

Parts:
C1, C3, C4: 100nF; C_0402_1005Metric
C2: 10nF; C_0402_1005Metric
C5: 10uF; C_0805_2012Metric
FB1: FerriteBead; R_0402_1005Metric
J1: Header-2x5; PinHeader_2x05_P2.54mm_Vertical
R1: 10k; R_0402_1005Metric
U1: ICM-42688-P; LGA-14_3x2.5mm_P0.5mm_LayoutBorder3x4y
U2: DPS310; Bosch_LGA-8_2x2.5mm_P0.65mm_ClockwisePinNumbering

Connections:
+3V3: C1.1, C2.1, C3.1, C4.1, C5.1, FB1.2, R1.2, U1.13 (VDDIO), U1.14 (VDD), U2.2 (CSB), U2.6 (VDDIO), U2.8 (VDD)
+3V3_RAW: FB1.1, J1.1 (3V3)
CS_IMU: J1.6 (CS), R1.1, U1.9 (CS)
GND: C1.2, C2.2, C3.2, C4.2, C5.2, J1.2 (GND), J1.10 (GND), U1.5 (GND), U2.1 (GND), U2.5 (SDO_ADDR), U2.7 (GND2)
INT_IMU: J1.7 (INT), U1.1 (INT1)
MISO: J1.5 (MISO), U1.11 (SDO)
MOSI: J1.4 (MOSI), U1.12 (SDI)
SCK: J1.3 (SCK), U1.10 (SCLK)
SCL: J1.9 (SCL), U2.4 (SCL)
SDA: J1.8 (SDA), U2.3 (SDA)

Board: 2 copper layers, 14 parts (0 on the bottom side), 10 nets, no tracks yet.

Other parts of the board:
H1, H2, H3, H4: M3; MountingHole_3.2mm_M3
